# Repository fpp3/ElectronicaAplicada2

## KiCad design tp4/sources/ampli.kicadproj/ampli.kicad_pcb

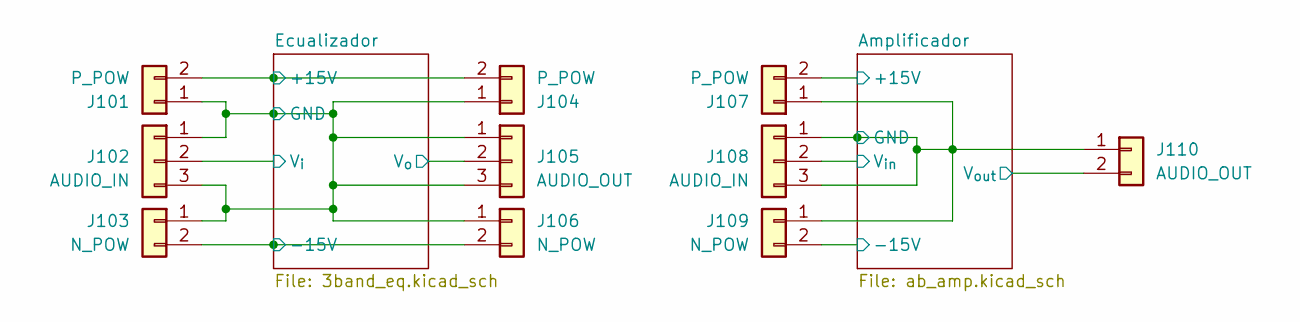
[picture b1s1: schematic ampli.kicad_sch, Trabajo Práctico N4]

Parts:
J101, J104, J107: P_POW; PinHeader_1x02_P2.54mm_Vertical
J102, J108: AUDIO_IN; PinHeader_1x03_P2.54mm_Vertical
J103, J106, J109: N_POW; PinHeader_1x02_P2.54mm_Vertical
J105: AUDIO_OUT; PinHeader_1x03_P2.54mm_Vertical
J110: AUDIO_OUT; TerminalBlock_Phoenix_MKDS-1,5-2-5.08_1x02_P5.08mm_Horizont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

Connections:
/Amplificador/+15V: J107.2; also elsewhere on the board
/Amplificador/-15V: J109.2; also elsewhere on the board
/Amplificador/GND: J107.1, J108.1, J108.3, J109.1, J110.1; also elsewhere on the board
/Amplificador/V_{in}: J108.2; also elsewhere on the board
/Amplificador/V_{out}: J110.2; also elsewhere on the board
/Ecualizador/+15V: J101.2, J104.2; also elsewhere on the board
/Ecualizador/-15V: J103.2, J106.2; also elsewhere on the board
/Ecualizador/GND: J101.1, J102.1, J102.3, J103.1, J104.1, J105.1, J105.3, J106.1; also elsewhere on the board
/Ecualizador/V_{i}: J102.2; also elsewhere on the board
/Ecualizador/V_{o}: J105.2; also elsewhere on the board

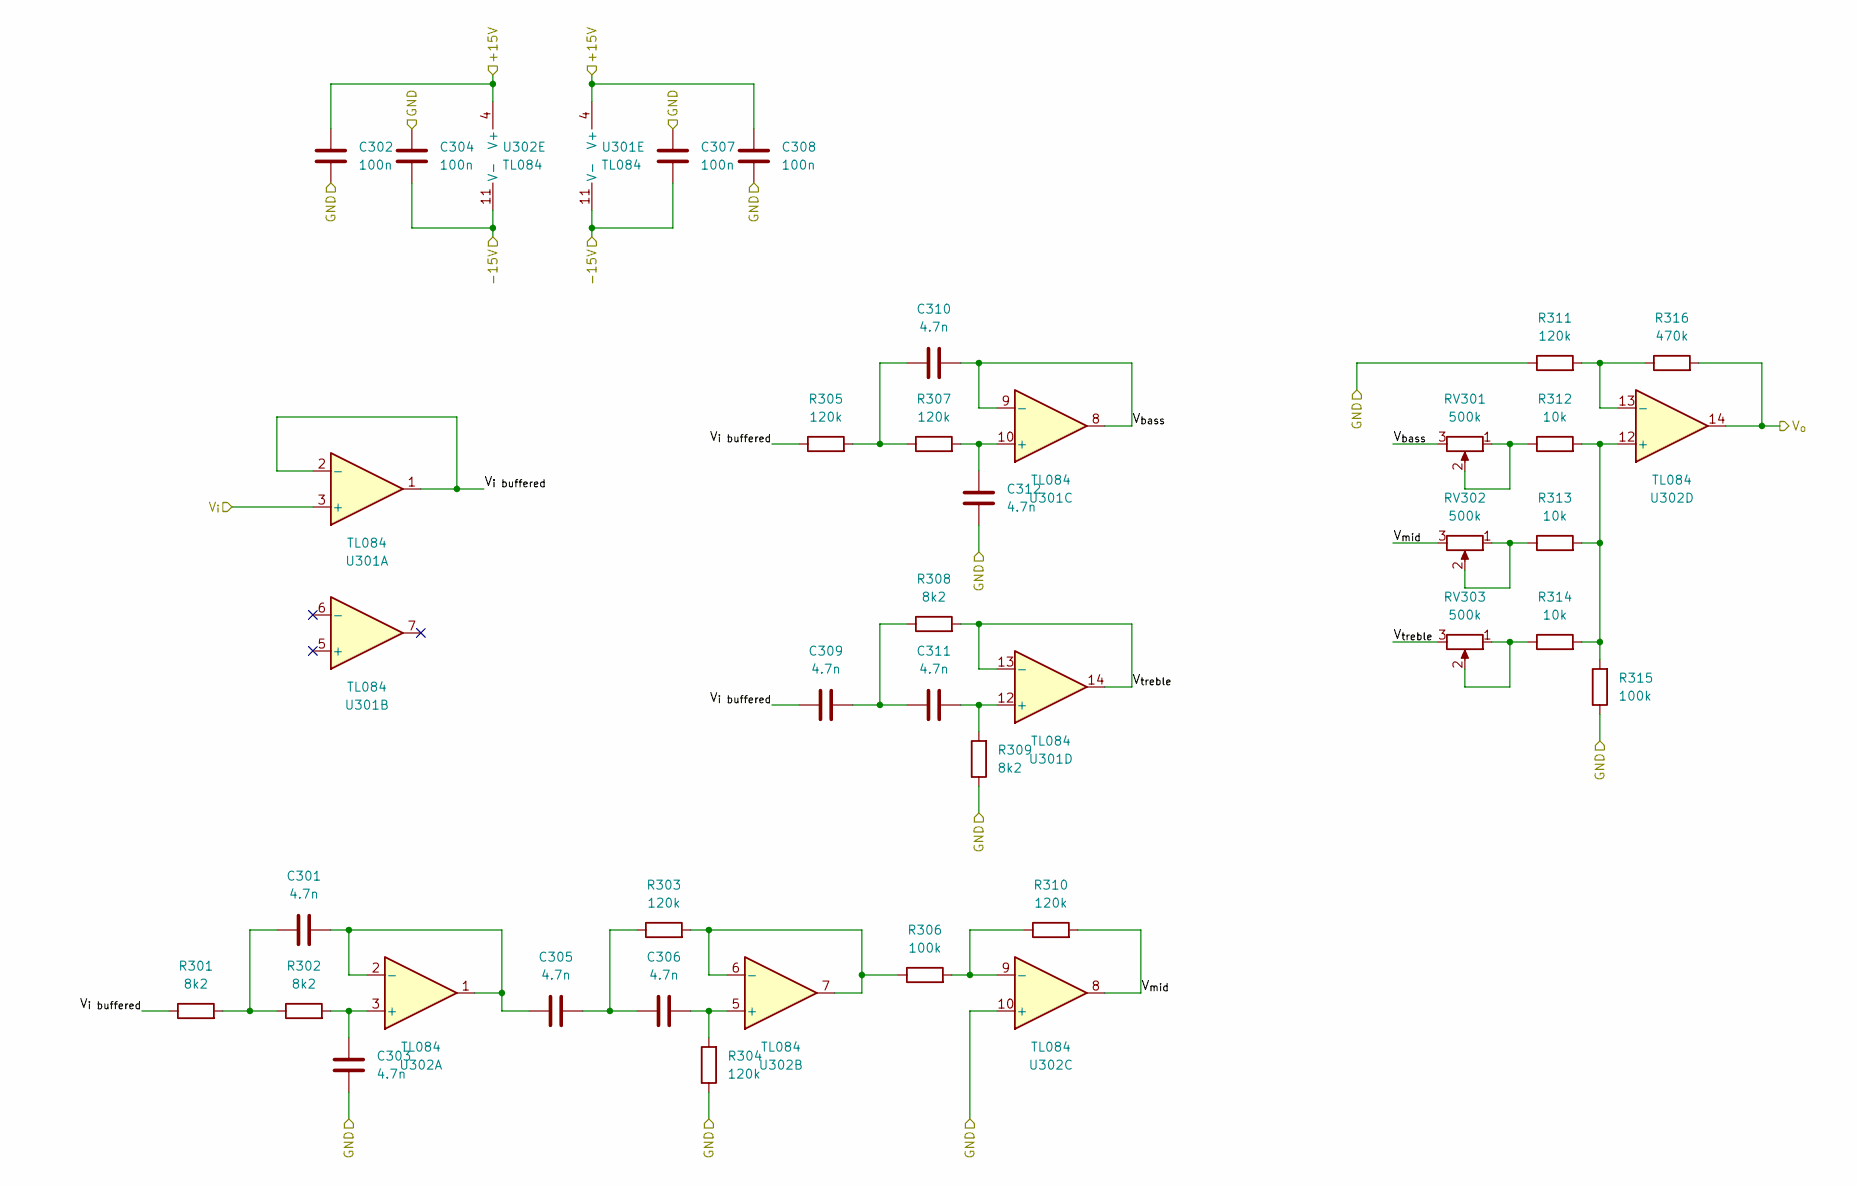
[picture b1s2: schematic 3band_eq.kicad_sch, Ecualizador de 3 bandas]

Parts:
C301, C303, C305, C306, C309, C310, C311, C312: 4.7n; C_Rect_L7.2mm_W2.5mm_P5.00mm
C302, C304, C307, C308: 100n; C_Disc_D5.0mm_W2.5mm_P2.50mm
R301, R302, R308, R309: 8k2; R_Axial_DIN0207_L6.3mm_D2.5mm_P10.16mm_Horizontal
R303, R304, R305, R307, R310, R311: 120k; R_Axial_DIN0207_L6.3mm_D2.5mm_P10.16mm_Horizontal
R306, R315: 100k; R_Axial_DIN0207_L6.3mm_D2.5mm_P10.16mm_Horizontal
R312, R313, R314: 10k; R_Axial_DIN0207_L6.3mm_D2.5mm_P10.16mm_Horizontal
R316: 470k; R_Axial_DIN0207_L6.3mm_D2.5mm_P10.16mm_Horizontal
RV301, RV302, RV303: 500k; Potentiometer_Omeg_PC16BU_Vertical
U301, U302: TL084; DIP-14_W7.62mm_Socket_LongPads

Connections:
/Ecualizador/+15V: C302.1, C308.1, U301.4 (V+), U302.4 (V+); also elsewhere on the board
/Ecualizador/-15V: C304.2, C307.2, U301.11 (V-), U302.11 (V-); also elsewhere on the board
/Ecualizador/GND: C302.2, C303.1, C304.1, C307.1, C308.2, C312.1, R304.1, R309.1, R311.1, R315.1, U302.10 (+); also elsewhere on the board
/Ecualizador/V_{bass}: C310.2, RV301.3, U301.8, U301.9 (-)
/Ecualizador/V_{i buffered}: C309.1, R301.1, R305.1, U301.1, U301.2 (-)
/Ecualizador/V_{i}: U301.3 (+); also elsewhere on the board
/Ecualizador/V_{mid}: R310.2, RV302.3, U302.8
/Ecualizador/V_{o}: R316.2, U302.14; also elsewhere on the board
/Ecualizador/V_{treble}: R308.2, RV303.3, U301.13 (-), U301.14
unnamed: C301.1, R301.2, R302.1
unnamed: C305.2, C306.2, R303.1
unnamed: C309.2, C311.2, R308.1
unnamed: C310.1, R305.2, R307.1
unnamed: R312.1, RV301.1, RV301.2
unnamed: R313.1, RV302.1, RV302.2
unnamed: R314.1, RV303.1, RV303.2
unnamed: C312.2, R307.2, U301.10 (+)
unnamed: C311.1, R309.2, U301.12 (+)
unnamed: C303.2, R302.2, U302.3 (+)
unnamed: C301.2, C305.1, U302.1, U302.2 (-)
unnamed: C306.1, R304.2, U302.5 (+)
unnamed: R303.2, R306.1, U302.6 (-), U302.7
unnamed: R306.2, R310.1, U302.9 (-)
unnamed: R312.2, R313.2, R314.2, R315.2, U302.12 (+)
unnamed: R311.2, R316.1, U302.13 (-)

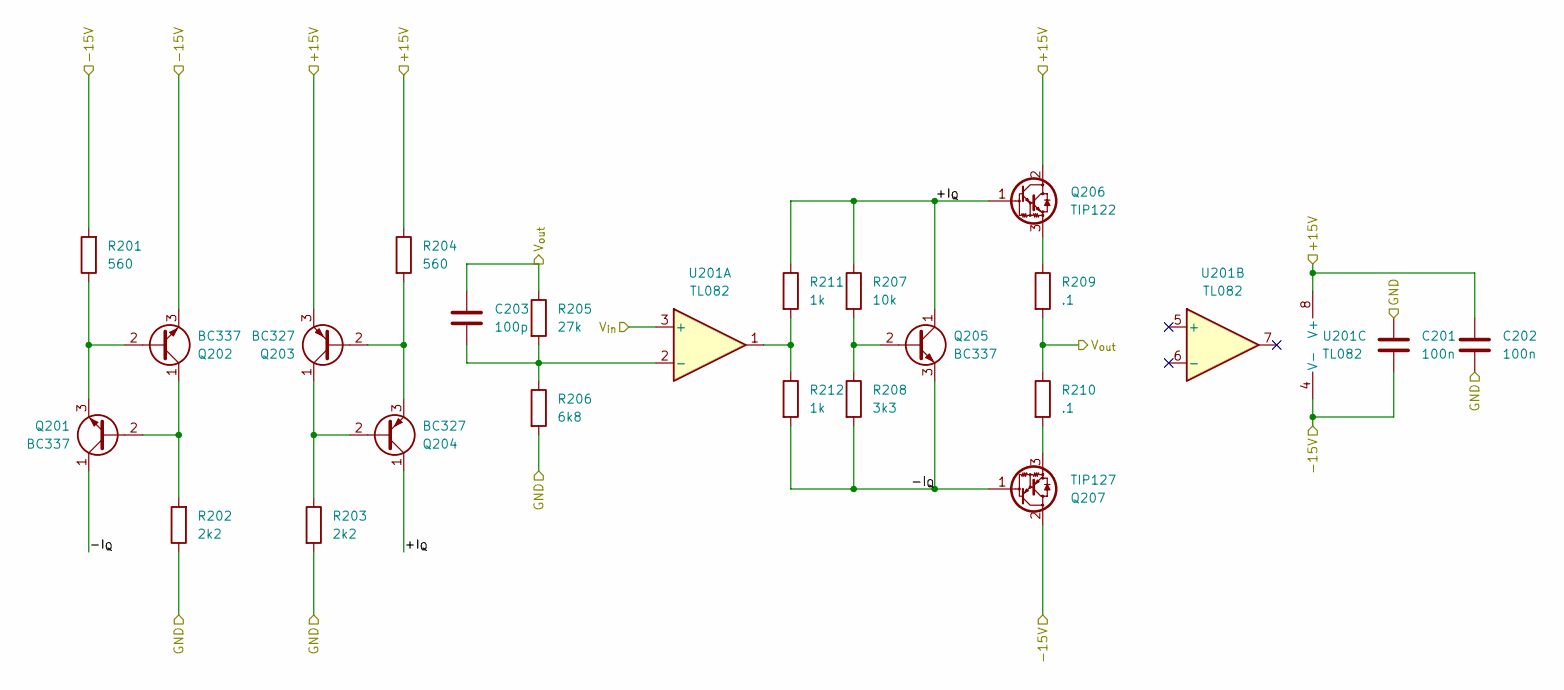
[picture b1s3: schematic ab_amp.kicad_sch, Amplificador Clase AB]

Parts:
C201, C202: 100n; C_Disc_D5.0mm_W2.5mm_P2.50mm
C203: 100p; C_Disc_D5.0mm_W2.5mm_P2.50mm
Q201, Q202, Q205: BC337; TO-92_Wide
Q203, Q204: BC327; TO-92_Wide
Q206: TIP122; TO-220-3_Vertical
Q207: TIP127; TO-220-3_Vertical
R201, R204: 560; R_Axial_DIN0207_L6.3mm_D2.5mm_P10.16mm_Horizontal
R202, R203: 2k2; R_Axial_DIN0207_L6.3mm_D2.5mm_P10.16mm_Horizontal
R205: 27k; R_Axial_DIN0207_L6.3mm_D2.5mm_P10.16mm_Horizontal
R206: 6k8; R_Axial_DIN0207_L6.3mm_D2.5mm_P10.16mm_Horizontal
R207: 10k; R_Axial_DIN0207_L6.3mm_D2.5mm_P10.16mm_Horizontal
R208: 3k3; R_Axial_DIN0207_L6.3mm_D2.5mm_P10.16mm_Horizontal
R209, R210: .1; R_Axial_DIN0516_L15.5mm_D5.0mm_P30.48mm_Horizontal
R211, R212: 1k; R_Axial_DIN0207_L6.3mm_D2.5mm_P10.16mm_Horizontal
U201: TL082; DIP-8_W7.62mm_Socket_LongPads

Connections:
/Amplificador/+15V: C202.1, Q203.3 (E), Q206.2 (C), R204.1, U201.8 (V+); also elsewhere on the board
/Amplificador/+I_{Q}: Q204.1 (C), Q205.1 (C), Q206.1 (B), R207.1, R211.1
/Amplificador/-15V: C201.2, Q202.3 (E), Q207.2 (C), R201.2, U201.4 (V-); also elsewhere on the board
/Amplificador/-I_{Q}: Q201.1 (C), Q205.3 (E), Q207.1 (B), R208.2, R212.2
/Amplificador/GND: C201.1, C202.2, R202.1, R203.2, R206.2; also elsewhere on the board
/Amplificador/V_{in}: U201.3 (+); also elsewhere on the board
/Amplificador/V_{out}: C203.1, R205.1, R209.2, R210.1; also elsewhere on the board
unnamed: Q201.2 (B), Q202.1 (C), R202.2
unnamed: Q201.3 (E), Q202.2 (B), R201.1
unnamed: Q203.2 (B), Q204.3 (E), R204.2
unnamed: Q203.1 (C), Q204.2 (B), R203.1
unnamed: Q205.2 (B), R207.2, R208.1
unnamed: Q206.3 (E), R209.1
unnamed: Q207.3 (E), R210.2
unnamed: R211.2, R212.1, U201.1
unnamed: C203.2, R205.2, R206.1, U201.2 (-)

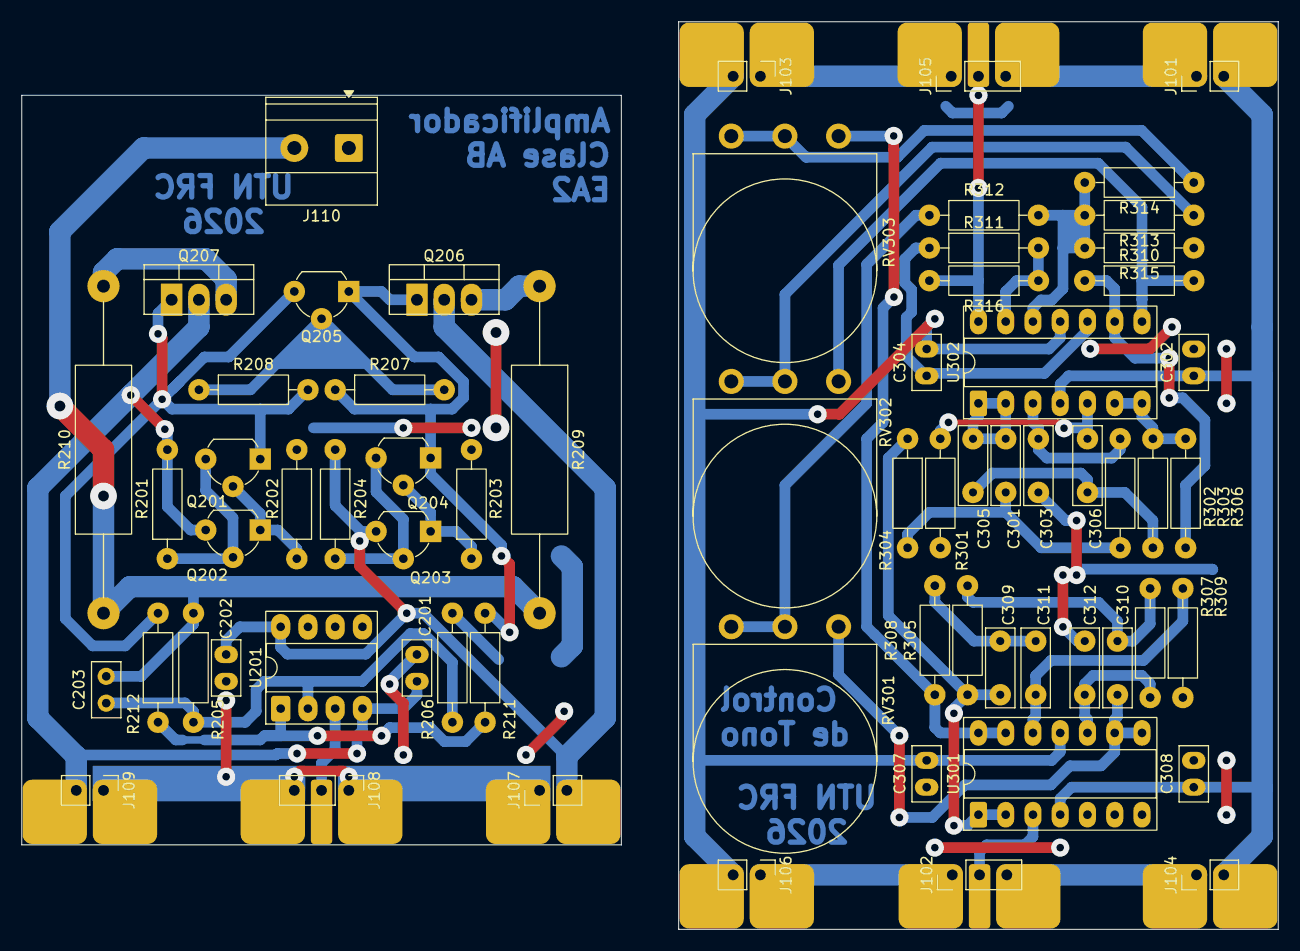
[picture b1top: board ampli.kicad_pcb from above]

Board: 2 copper layers, 117.1 x 84.6 mm, 66 parts (0 on the bottom side), 41 nets.

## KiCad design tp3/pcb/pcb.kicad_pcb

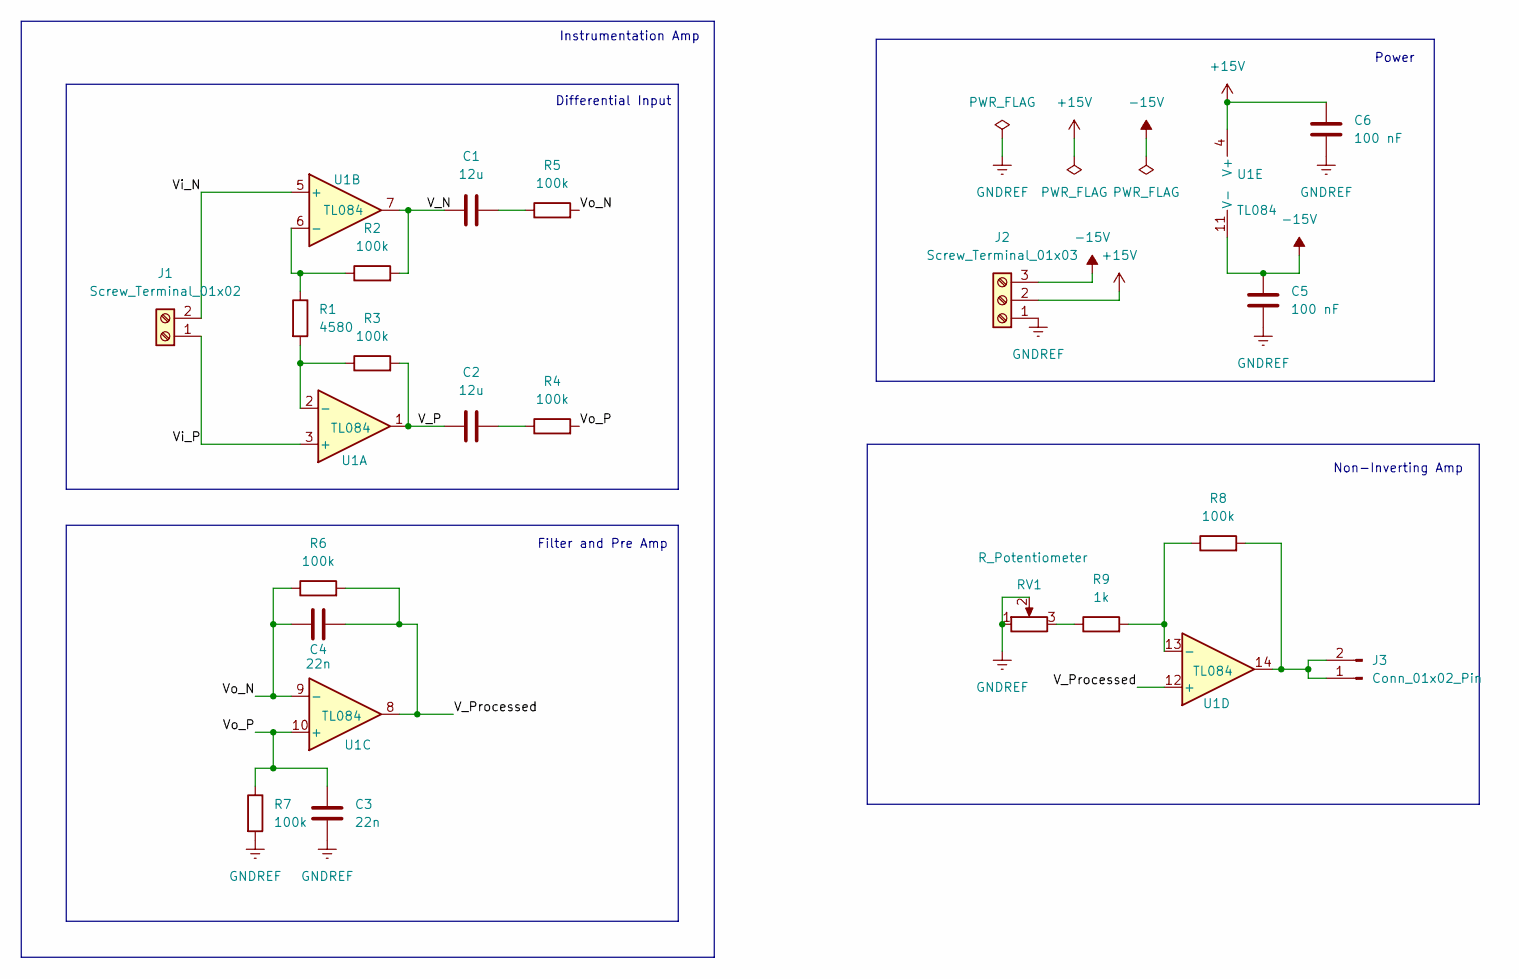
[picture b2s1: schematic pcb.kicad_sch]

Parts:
C1, C2: 12u; C_Disc_D5.0mm_W2.5mm_P2.50mm
C3, C4: 22n; C_Disc_D5.0mm_W2.5mm_P2.50mm
C5, C6: 100 nF; C_Disc_D5.0mm_W2.5mm_P2.50mm
J1: Screw_Terminal_01x02; TerminalBlock_MaiXu_MX126-5.0-02P_1x02_P5.00mm
J2: Screw_Terminal_01x03; TerminalBlock_MaiXu_MX126-5.0-03P_1x03_P5.00mm
J3: Conn_01x02_Pin; PinHeader_1x02_P2.54mm_Vertical
R1: 4580; R_Axial_DIN0207_L6.3mm_D2.5mm_P10.16mm_Horizontal
R2, R3, R4, R5, R6, R7, R8: 100k; R_Axial_DIN0207_L6.3mm_D2.5mm_P10.16mm_Horizontal
R9: 1k; R_Axial_DIN0207_L6.3mm_D2.5mm_P10.16mm_Horizontal
RV1: R_Potentiometer; Potentiometer_Bourns_3296W_Vertical
U1: TL084; DIP-14_W7.62mm_Socket_LongPads

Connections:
+15V: C6.1, J2.2, U1.4 (V+)
-15V: C5.1, J2.3, U1.11 (V-)
/V_N: C1.1, R2.2, U1.7
/V_P: C2.2, R3.2, U1.1
/V_Processed: C4.2, R6.2, U1.8, U1.12 (+)
/Vi_N: J1.2, U1.5 (+)
/Vi_P: J1.1, U1.3 (+)
/Vo_N: C4.1, R5.2, R6.1, U1.9 (-)
/Vo_P: C3.1, R4.2, R7.1, U1.10 (+)
GNDREF: C3.2, C5.2, C6.2, J2.1, R7.2, RV1.1, RV1.2
unnamed: C1.2, R5.1
unnamed: C2.1, R4.1
unnamed: J3.1, J3.2, R8.2, U1.14
unnamed: R9.1, RV1.3
unnamed: R1.2, R3.1, U1.2 (-)
unnamed: R1.1, R2.1, U1.6 (-)
unnamed: R8.1, R9.2, U1.13 (-)

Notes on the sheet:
Instrumentation Amp
Filter and Pre Amp
Power
Non-Inverting Amp
Differential Input

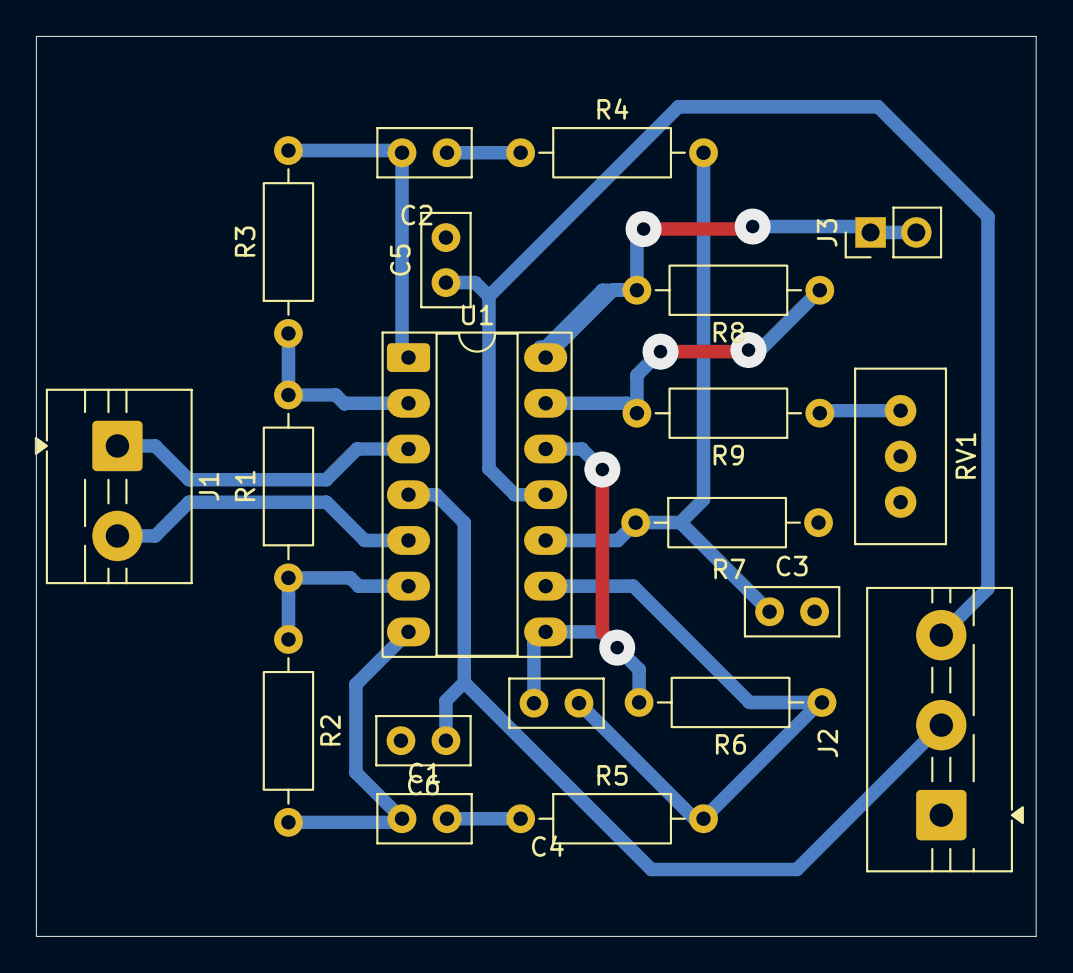
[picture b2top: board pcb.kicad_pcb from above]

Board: 2 copper layers, 55.5 x 50.0 mm, 20 parts (0 on the bottom side), 17 nets.

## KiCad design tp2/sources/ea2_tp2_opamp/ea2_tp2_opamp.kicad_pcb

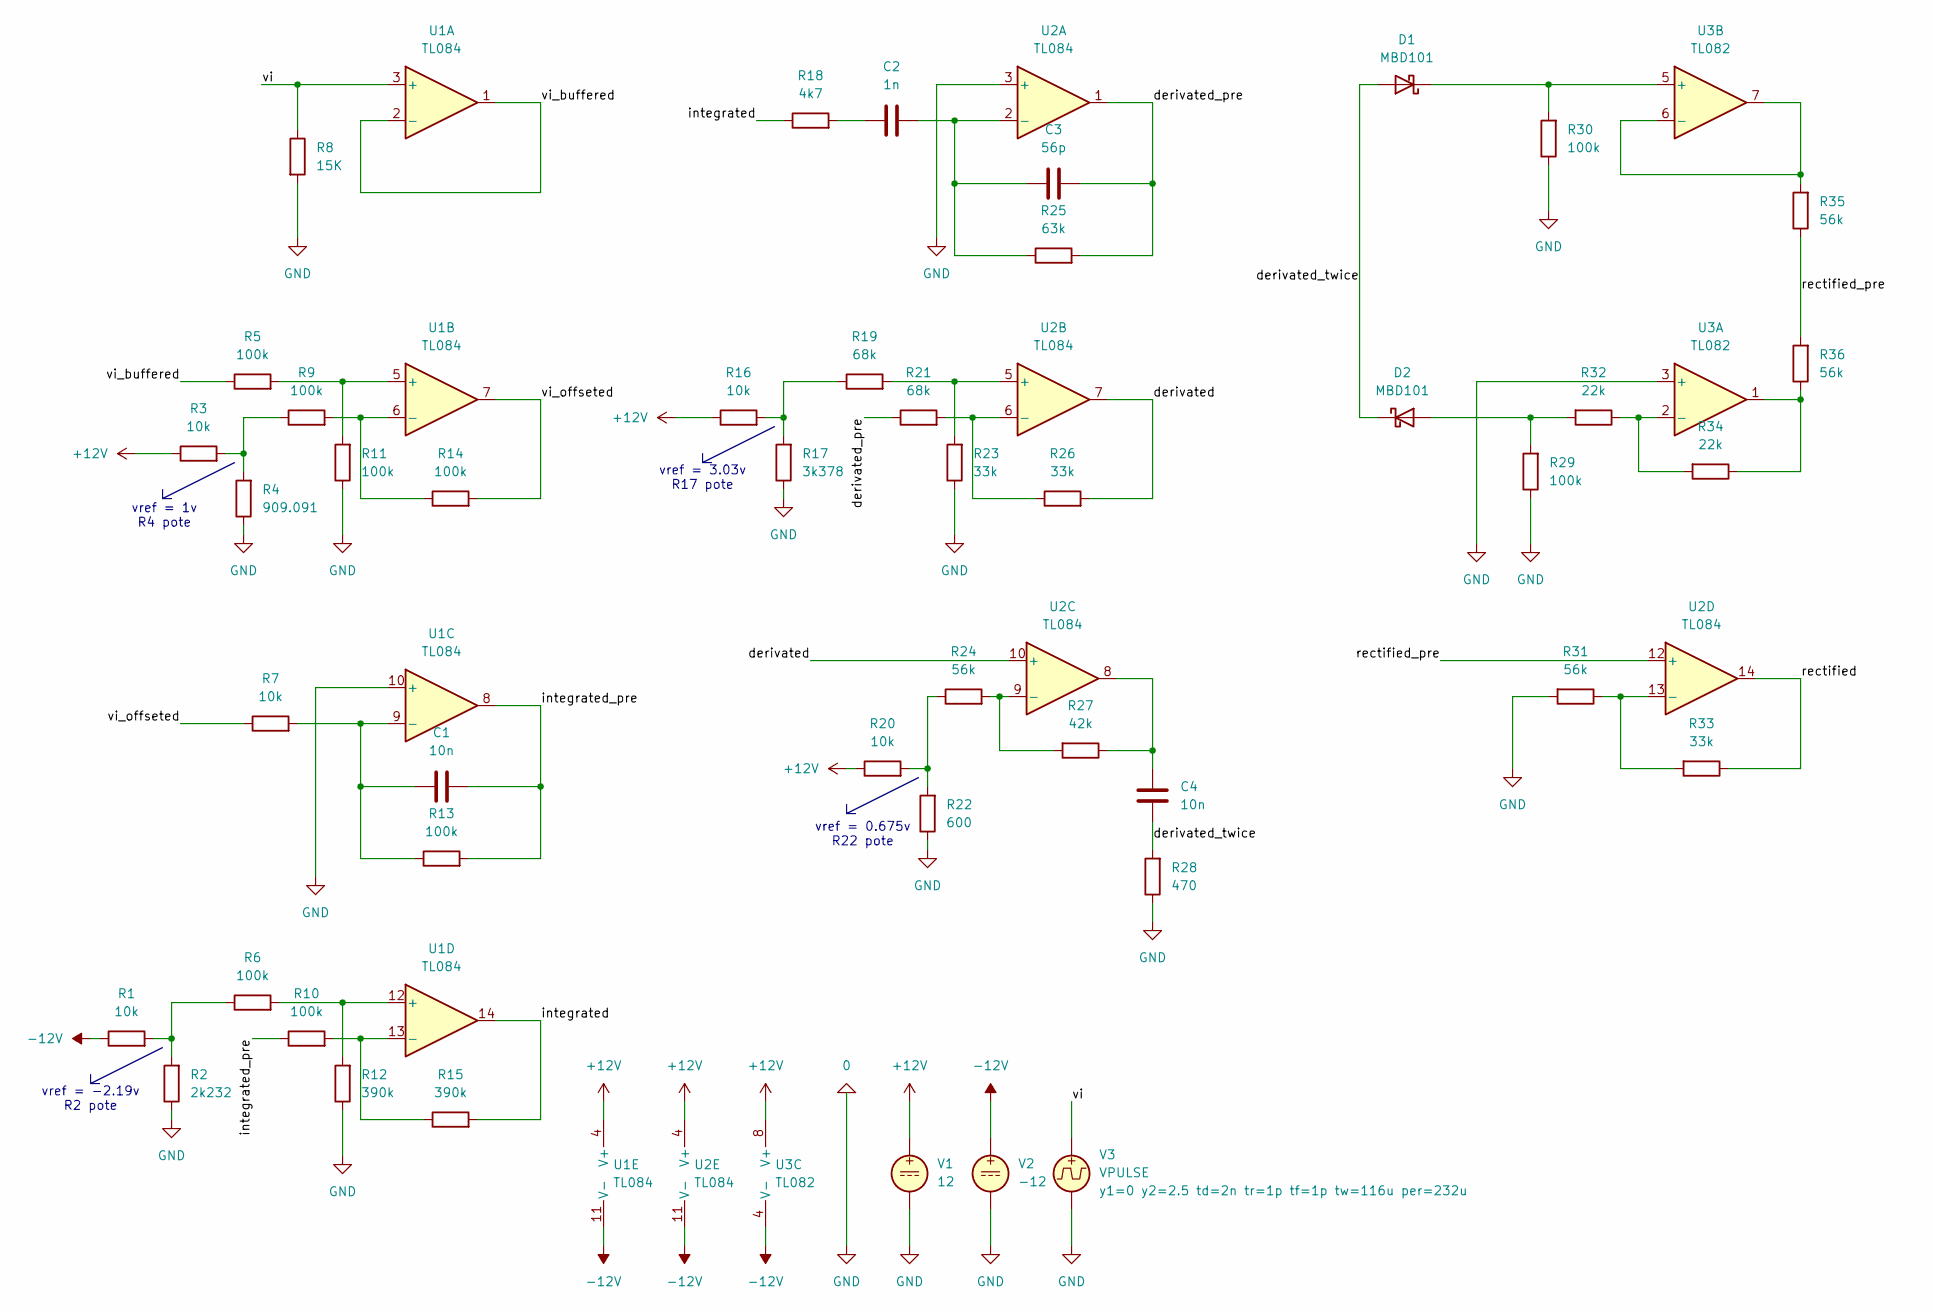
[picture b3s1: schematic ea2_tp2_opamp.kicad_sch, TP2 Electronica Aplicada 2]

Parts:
C1, C4: 10n; C_Disc_D4.7mm_W2.5mm_P5.00mm
C2: 1n; C_Disc_D4.7mm_W2.5mm_P5.00mm
C3: 56p; C_Disc_D4.7mm_W2.5mm_P5.00mm
D1, D2: MBD101; TO-92-2
R1, R3, R7, R16, R20: 10k; R_Axial_DIN0207_L6.3mm_D2.5mm_P10.16mm_Horizontal
R2: 2k232; Potentiometer_Bourns_3296W_Vertical
R4: 909.091; Potentiometer_Bourns_3296W_Vertical
R5, R6, R9, R10, R11, R13, R14, R29, R30: 100k; R_Axial_DIN0207_L6.3mm_D2.5mm_P10.16mm_Horizontal
R8: 15K; R_Axial_DIN0207_L6.3mm_D2.5mm_P10.16mm_Horizontal
R12, R15: 390k; R_Axial_DIN0207_L6.3mm_D2.5mm_P10.16mm_Horizontal
R17: 3k378; Potentiometer_Bourns_3296W_Vertical
R18: 4k7; R_Axial_DIN0207_L6.3mm_D2.5mm_P10.16mm_Horizontal
R19, R21: 68k; R_Axial_DIN0207_L6.3mm_D2.5mm_P10.16mm_Horizontal
R22: 600; Potentiometer_Bourns_3296W_Vertical
R23, R26, R33: 33k; R_Axial_DIN0207_L6.3mm_D2.5mm_P10.16mm_Horizontal
R24, R31, R35, R36: 56k; R_Axial_DIN0207_L6.3mm_D2.5mm_P10.16mm_Horizontal
R25: 63k; R_Axial_DIN0207_L6.3mm_D2.5mm_P10.16mm_Horizontal
R27: 42k; R_Axial_DIN0207_L6.3mm_D2.5mm_P10.16mm_Horizontal
R28: 470; R_Axial_DIN0207_L6.3mm_D2.5mm_P10.16mm_Horizontal
R32, R34: 22k; R_Axial_DIN0207_L6.3mm_D2.5mm_P10.16mm_Horizontal
U1, U2: TL084; DIP-14_W7.62mm
U3: TL082; DIP-8_W7.62mm
V1: 12
V2: -12
V3: VPULSE

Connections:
0: R2.1, R4.1, R8.2, R11.1, R12.1, R17.1, R22.1, R22.3, R23.1, R28.1, R29.1, R30.1, R31.2, U1.10 (+), U2.3 (+), U3.3 (+), V1.2, V2.2, V3.2
+12V: R3.1, R16.1, R20.1, U1.4 (V+), U2.4 (V+), U3.8 (V+), V1.1
-12V: R1.1, U1.11 (V-), U2.11 (V-), U3.4 (V-), V2.1
/derivated: R26.2, U2.7, U2.10 (+)
/derivated_pre: C3.2, R21.1, R25.2, U2.1
/derivated_twice: C4.1, D1.2 (A), D2.1 (K), R28.2
/integrated: R15.2, R18.1, U1.14
/integrated_pre: C1.2, R10.1, R13.2, U1.8
/rectified: R33.1, U2.14
/rectified_pre: R35.1, R36.2, U2.12 (+)
/vi: R8.1, U1.3 (+), V3.1
/vi_buffered: R5.1, U1.1, U1.2 (-)
/vi_offseted: R7.1, R14.2, U1.7
unnamed: C2.1, R18.2
unnamed: C4.2, R27.1, U2.8
unnamed: D1.1 (K), R30.2, U3.5 (+)
unnamed: D2.2 (A), R29.2, R32.2
unnamed: R1.2, R2.2, R6.1
unnamed: R3.2, R4.2, R9.1
unnamed: R16.2, R17.2, R19.1
unnamed: R20.2, R22.2, R24.1
unnamed: R34.1, R36.1, U3.1
unnamed: R5.2, R11.2, U1.5 (+)
unnamed: R9.2, R14.1, U1.6 (-)
unnamed: C1.1, R7.2, R13.1, U1.9 (-)
unnamed: R6.2, R12.2, U1.12 (+)
unnamed: R10.2, R15.1, U1.13 (-)
unnamed: C2.2, C3.1, R25.1, U2.2 (-)
unnamed: R19.2, R23.2, U2.5 (+)
unnamed: R21.2, R26.1, U2.6 (-)
unnamed: R24.2, R27.2, U2.9 (-)
unnamed: R31.1, R33.2, U2.13 (-)
unnamed: R32.1, R34.2, U3.2 (-)
unnamed: R35.2, U3.6 (-), U3.7

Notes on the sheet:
vref = 3.03v R17 pote
vref = 0.675v R22 pote
vref = 1v R4 pote
vref = -2.19v R2 pote

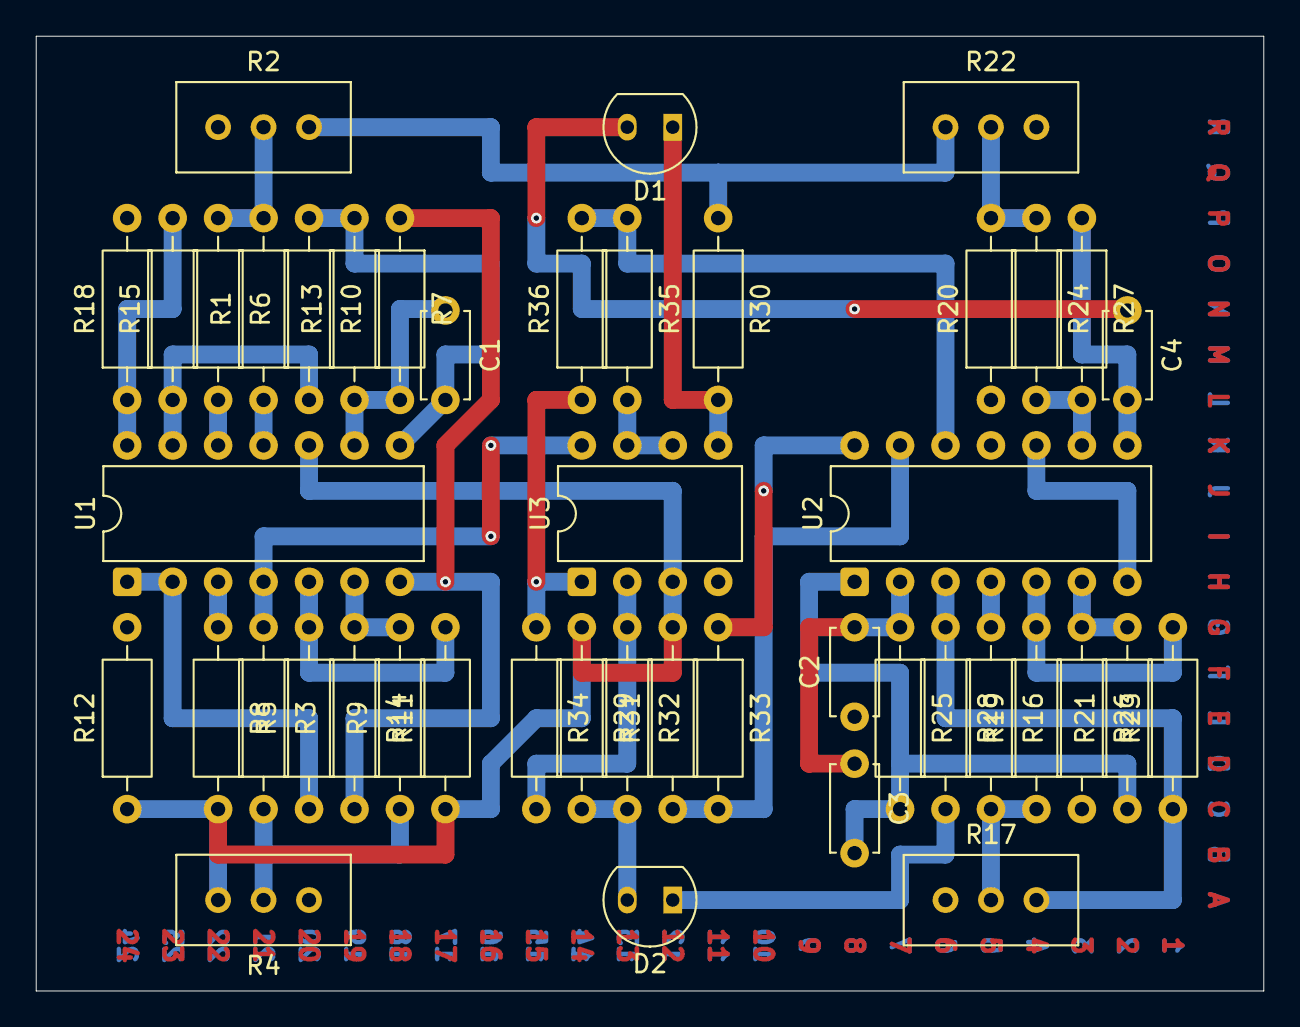
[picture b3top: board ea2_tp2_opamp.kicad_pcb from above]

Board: 4 copper layers, 68.6 x 53.3 mm, 45 parts (0 on the bottom side), 34 nets.

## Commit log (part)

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2026-04-15 chore: setup latex project structure and initial report template for TP1
2026-04-16 consigna reubicada a carpeta aparte
2026-04-16 Agrega archivo de simulacion
2026-04-21 Corrije estructura de y archivos para seguir pautas del secreto.md
2026-04-21 Agrega circuito dibujado en tikz
2026-04-21 Agrega archivo correcto de simulacion
2026-04-21 Corrige circuito dibujado
2026-04-21 Escribe los resultados obtenidos de simulacion
2026-04-21 Dibuja cuadros BODE de simulacion
2026-04-22 Agrega capturas del osciloscopio
2026-04-22 Corrige estructura de archivos y figuras
2026-04-22 Modifica los capitulos para usar siunitx
2026-04-22 borrada seccion de calculo de componnetes y actualzada tabla de medicion de parametros
2026-04-22 Extiende introd. para contrastar en conclusion
2026-04-22 Explica de que se trata el circuito
2026-04-22 Redacta mejor la introduccion a simulacion
2026-04-22 Escribe conclusion
2026-04-22 Corrige grafica respuesta en frecuencia y prepara para lab
2026-04-22 Expande la seccion de mediciones para incluir fotos
2026-04-22 Corrige legajo ignacio
2026-04-22 feat: agrega esquemas TikZ de medición y organiza estructura del proyecto
2026-04-23 arreglado diagrama de medicion zi y zo
2026-04-23 agregado componente reemplazado
2026-04-23 Termina el tp1
2026-04-27 agregada simulacion en LTspice TP2 y circuito en Kicad
2026-04-29 Correcciones menores tp1
2026-05-02 tp2: agrega esquematico, simulacion y plots
2026-05-06 tp2: optimizacion de enrutado de placa
2026-05-07 tp2: Metanse la pcb en el orto
2026-05-07 cositas lol
2026-05-07 tp2: agrega plots
2026-05-07 plots y anexo sch
2026-05-13 agregado el esquematico de forma horizontala
2026-05-14 soucionado problema de csv con ;
2026-05-15 agregados todos los tikz a sources
2026-05-17 tp2: Termina cap diseño, calculos y sim
2026-05-19 agregado calculo de resistencias offset integrador
2026-05-20 tp2: fin
2026-05-21 Corrige plots con ticks superpuestos
2026-05-21 Corrige errores de ortografia
2026-05-21 tp2: correcciones menores
